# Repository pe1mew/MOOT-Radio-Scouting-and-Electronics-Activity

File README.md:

# 15th MOOT Radio Scouting and electronics activity repository

## Introduction

This repo contains all the games and activities shown and used at the Moot 2017 in Iceland. 
At the moment we are trying to get everything together, but it's not completely ready yet. 

Please come back later for more information.

## Licences

License other documents and files
---------------------------------
<br />This work is licensed under a <a rel="license" href="http://creativecommons.org/licenses/by-sa/4.0/">Creative Commons Attribution-ShareAlike 4.0 International License</a>.

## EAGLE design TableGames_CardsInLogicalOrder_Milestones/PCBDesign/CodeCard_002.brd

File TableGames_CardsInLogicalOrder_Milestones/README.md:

# Table games: Milestones
This game is part of the 15th MOOT Radio Scouting and electronics activity repository

## Introduction

This repo contains all the games and activities shown and used at the Moot 2017 in Iceland. 
At the moment we are trying to get everything together, but it's not completely ready yet. 

Please come back later for more information.

## Licence
Idea by Michael Kohlert (Micha), Germany, micha@scoutnet.de
<br />This work is licensed under a <a rel="license" href="http://creativecommons.org/licenses/by-sa/4.0/">Creative Commons Attribution-ShareAlike 4.0 International License</a>.

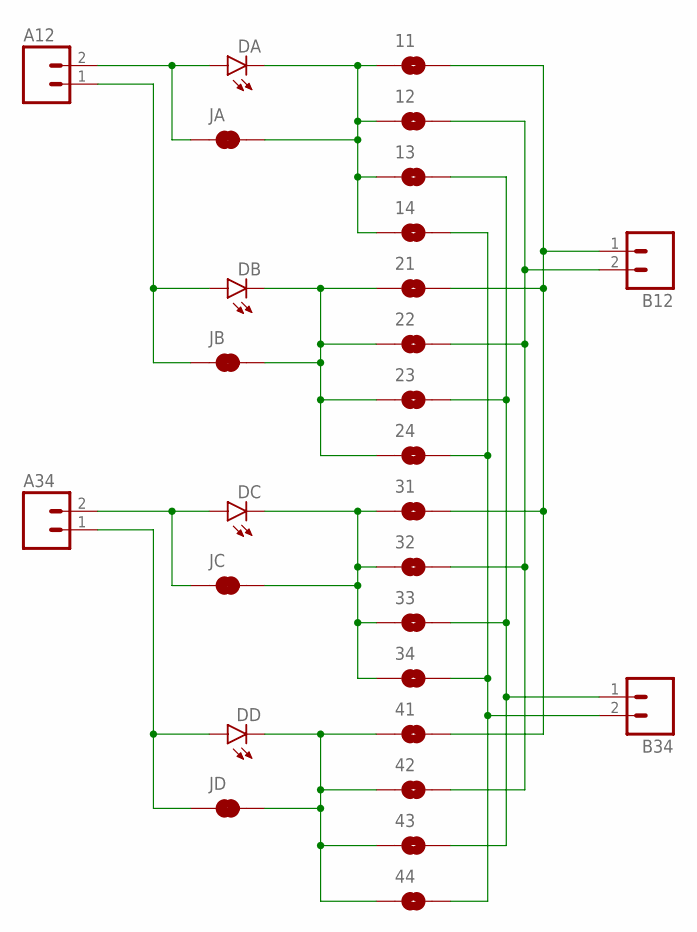
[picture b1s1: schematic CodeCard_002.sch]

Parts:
11, 12, 13, 14, 21, 22, 23, 24, 31, 32, 33, 34, 41, 42, 43, 44: JUMPER-PAD-2-NOROUND; PAD-JUMPER-2-NO_YES_SILK_ROUND
A12, A34: M02PTH3; 1X02_LONGPADS
B12, B34: M02PTH3; 1X02_LONGPADS
DA: LED1206; LED-1206
DB: LED1206; LED-1206
DC: LED1206; LED-1206
DD: LED1206; LED-1206
JA: JUMPER-PAD-2-NC_BY_TRACENO_SILK; PAD-JUMPER-2-NC_BY_TRACE_NO_SILK
JB: JUMPER-PAD-2-NC_BY_TRACENO_SILK; PAD-JUMPER-2-NC_BY_TRACE_NO_SILK
JC: JUMPER-PAD-2-NC_BY_TRACENO_SILK; PAD-JUMPER-2-NC_BY_TRACE_NO_SILK
JD: JUMPER-PAD-2-NC_BY_TRACENO_SILK; PAD-JUMPER-2-NC_BY_TRACE_NO_SILK

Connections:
D: 41.1, 42.1, 43.1, 44.1, DD.C, JD.2
unnamed: 11.1, 12.1, 13.1, 14.1, DA.C, JA.2
unnamed: 21.1, 22.1, 23.1, 24.1, DB.C, JB.2
unnamed: 31.1, 32.1, 33.1, 34.1, DC.C, JC.2
unnamed: 11.2, 21.2, 31.2, 41.2, B12.1
unnamed: 12.2, 22.2, 32.2, 42.2, B12.2
unnamed: 13.2, 23.2, 33.2, 43.2, B34.1
unnamed: 14.2, 24.2, 34.2, 44.2, B34.2
unnamed: A12.1, DB.A, JB.1
unnamed: A12.2, DA.A, JA.1
unnamed: A34.1, DD.A, JD.1
unnamed: A34.2, DC.A, JC.1

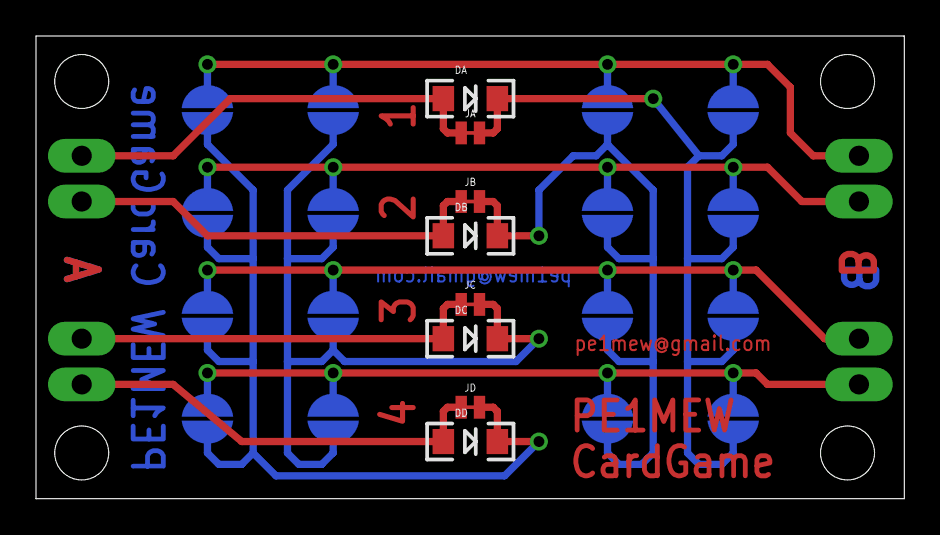
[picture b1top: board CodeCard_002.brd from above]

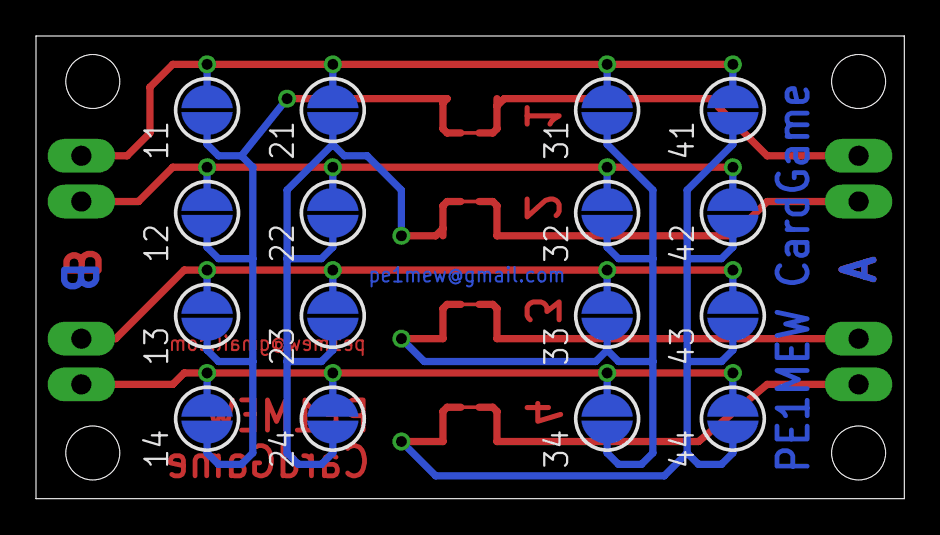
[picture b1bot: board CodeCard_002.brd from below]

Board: 2 copper layers, 48.2 x 25.7 mm, 28 parts (16 on the bottom side), 12 nets.

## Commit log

2017-07-12 :lollipop: Added .gitattributes & .gitignore files
2017-08-02 Update at MOOT
    we will update more the coming period

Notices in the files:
parts and their libraries:
SparkFun-LED: Licensing: Creative Commons ShareAlike 4.0 International - https://creativecommons.org/licenses/by-sa/4.0
